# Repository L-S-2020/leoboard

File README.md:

# Leoboard

A makroboard I designed as a christmas present and my first project using 3d printing / cad design.
You can find the case design on onshape under: 
https://cad.onshape.com/documents/f016138659585157d187dc39/w/5da7c9f47346b58de636040e/e/736dc8079a6dc26abaf89305?renderMode=0&uiState=69bc84548cc73f69bd25787e

## Features
- 6 MX Style switches
- buzzer (for sound)
- rotary encoder
- rgb leds 
- rp2040 based

Note: The code folder also includes kmk and the necessary addons, so it can be directly flashed to the rp2040.

## Standard key binds
The board has 3 switchable layers:
|Layer| Rotary button | Rotary encoder | Button 1 | Button 2 | Button 3 | Button 4 | Button 5 | Button 6 |
|--|--|--|--|--|--|--|--|--|
| 1 (normal) | Mute | Volume | Play/ Pause | Next song | Previous song | Win+Shift+S | Task manager | Lock pc |
|2 (gaming) |Discord mute| Volume | Mute | Discord audio off | Medal save clip | Screenshot | M | I |
|3 (premiere pro) | \ | Seek through frames | Add cut | Delete clip | Zoom in | Zoom out | Undo | Redo |
|Setings| must be hold down | -- | Layer 1 | Layer 2 | Layer 3 | LED on/off | LED breathe animation |LED rainbow animation |

## The story
One day as I was editing a video for the video club at my school (check out the [yt channel](https://www.youtube.com/@gsgwaldkirch4155)), I was annoyed by the standard key assignments of Premiere Pro. Especially using the arrow keys to seek through frames manually (i.e. for finding the excact startframe of a clip) is a really slow process, so I thought, wouldn't it be cool to have a rotary knob for that and then also to have a special key set for directly placing cuts and zooming in the timeline? 

So I the idea to design my own macroboard was born. I found a nice starting tutorial on [the hackclub blueprint website](https://blueprint.hackclub.com/), which showed the ground ideas of macroboard design.
As it was just two weeks before christmas back then, I thought it would also be cool to use the board as a christmas present.

So I got started with the pcb design using kicad. The design itself is based on the seed xiao rp2040 devboard, as it is the perfect size and also quite cheap. Additionally to my initial requirements (switches and rotary encoder), I came up with the idea to also add leds for light and a buzzer for playing startup sounds.

Then I designed the pcb board and searched in the jlcpcb parts library for suiting (and cheap) parts. 

As the order was on its way, I started designing the case using onshape.

I also created an assembled model in onshape, to test the dimensions.

After printing and assembling the final macropads, I learned that, it's not good to make the inner dimensions of your case exactly like the dimensions of your board ;) , but fortunately, I printed everything in pla, so after some heating using a hair dryer, I could fit the pcb inside.

I then wrote a script for it, using kmk, as I liked the idea of being able to quickly change some configurations, without having to recompile. 
[@SillyGoose123](https://github.com/SillyGoose123) is also currently working on a more powerful, rust-based firmware for the board with a web based settings interface, check it out [here](https://github.com/SillyGoose123/MacroBoard).

##
A big thanks to my cs teacher for letting me print out the cases using the 3dprinter in his office and to [@SillyGoose123](https://github.com/SillyGoose123) for printing out the keycaps.

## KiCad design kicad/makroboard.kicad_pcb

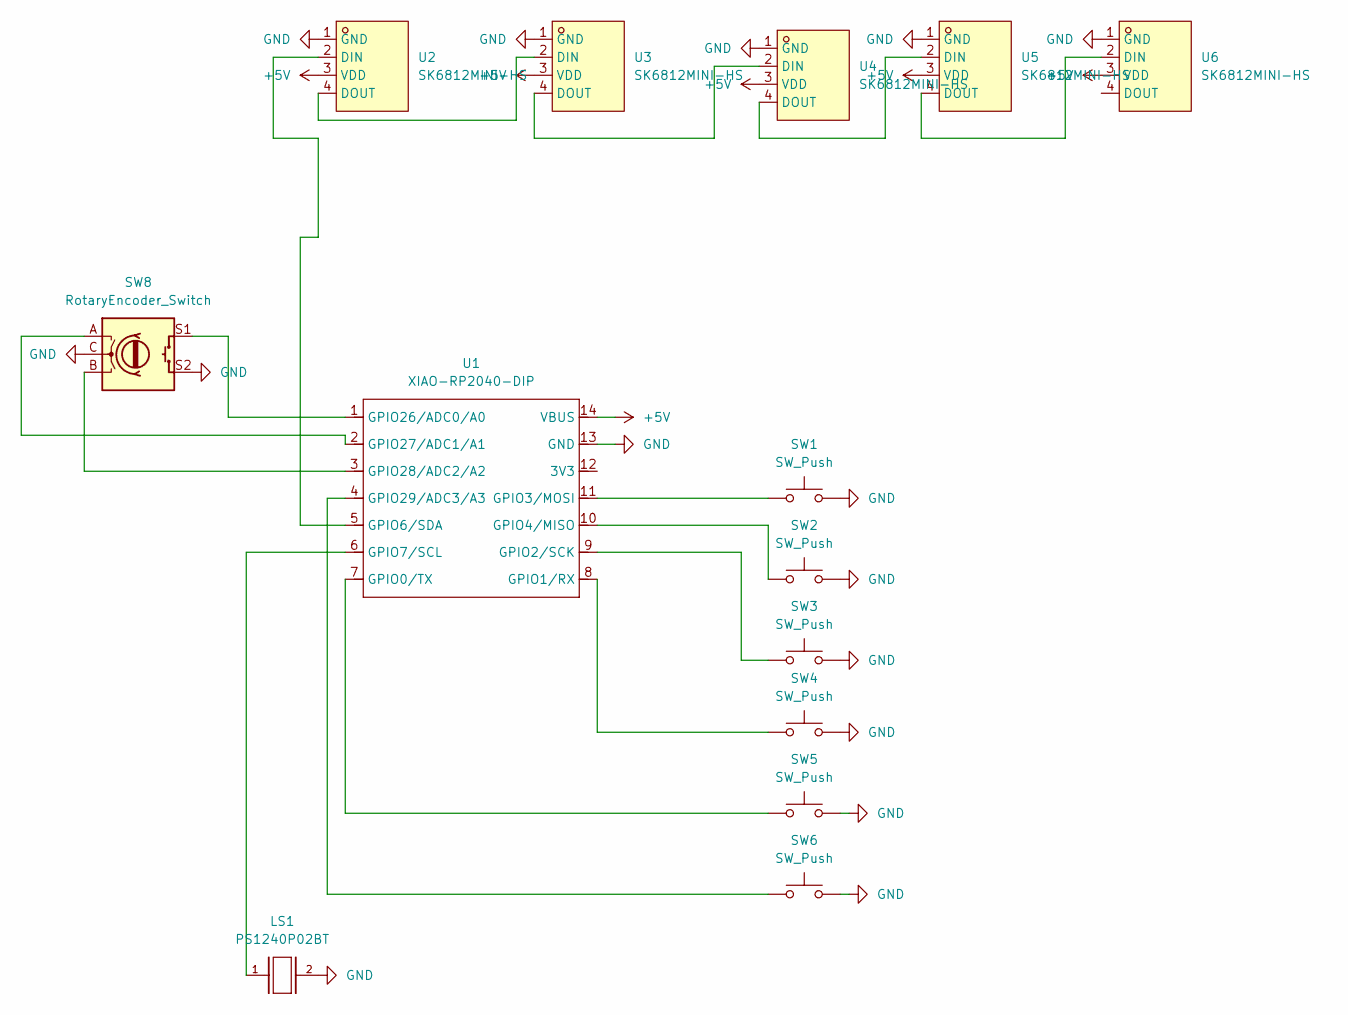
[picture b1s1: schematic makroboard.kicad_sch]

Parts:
LS1: PS1240P02BT; XDCR_PS1240P02BT
SW1, SW2, SW3, SW4, SW5, SW6: SW_Push; SW_Cherry_MX_1.00u_Plate
SW8: RotaryEncoder_Switch; RotaryEncoder_Alps_EC11E-Switch_Vertical_H20mm
U1: XIAO-RP2040-DIP
U2, U3, U4, U5, U6: SK6812MINI-HS; LED-SMD_4P-L3.5-W3.5-BR_SK6812MINI-HS; LCSC Part C2922787

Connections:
+5V: U1.14 (VBUS), U2.3 (VDD), U3.3 (VDD), U4.3 (VDD), U5.3 (VDD), U6.3 (VDD)
GND: LS1.2, SW1.2, SW2.2, SW3.2, SW4.2, SW5.2, SW6.2, SW8.C, SW8.S2, U1.13 (GND), U2.1 (GND), U3.1 (GND), U4.1 (GND), U5.1 (GND), U6.1 (GND)
unnamed: SW5.1, U1.7 (GPIO0/TX)
unnamed: SW4.1, U1.8 (GPIO1/RX)
unnamed: SW3.1, U1.9 (GPIO2/SCK)
unnamed: SW1.1, U1.11 (GPIO3/MOSI)
unnamed: SW2.1, U1.10 (GPIO4/MISO)
unnamed: U1.5 (GPIO6/SDA), U2.2 (DIN)
unnamed: LS1.1, U1.6 (GPIO7/SCL)
unnamed: SW8.S1, U1.1 (GPIO26/ADC0/A0)
unnamed: SW8.A, U1.2 (GPIO27/ADC1/A1)
unnamed: SW8.B, U1.3 (GPIO28/ADC2/A2)
unnamed: SW6.1, U1.4 (GPIO29/ADC3/A3)
unnamed: U2.4 (DOUT), U3.2 (DIN)
unnamed: U3.4 (DOUT), U4.2 (DIN)
unnamed: U4.4 (DOUT), U5.2 (DIN)
unnamed: U5.4 (DOUT), U6.2 (DIN)

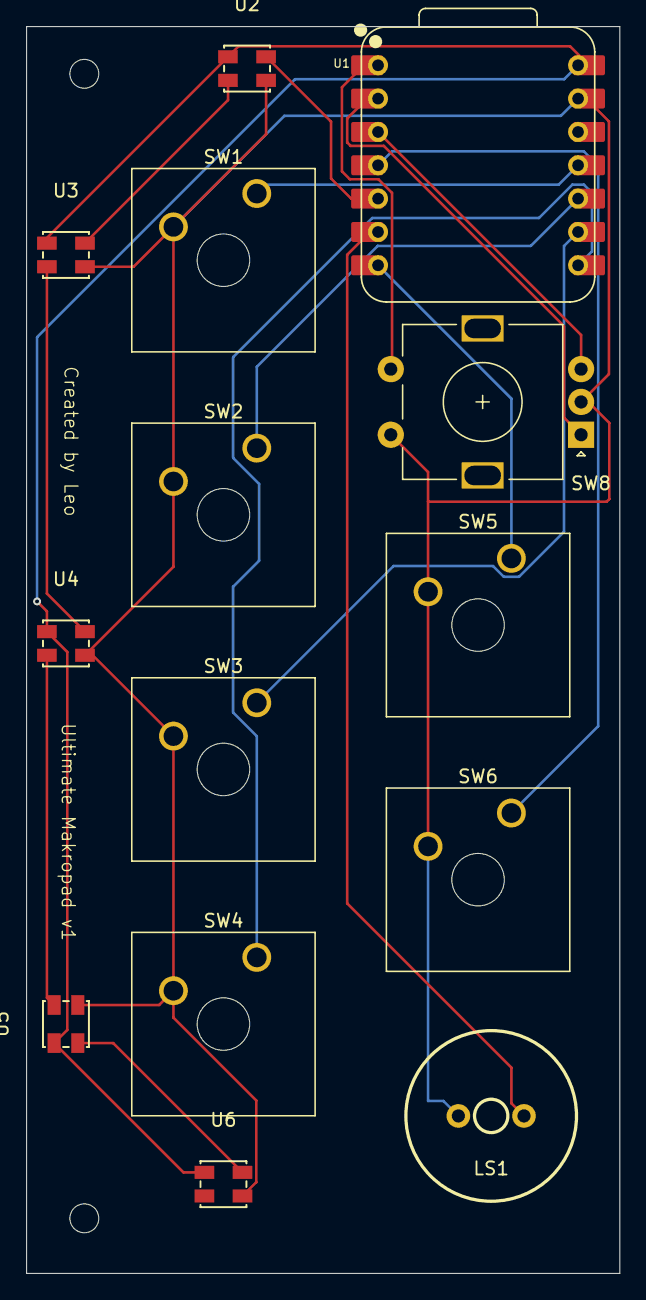
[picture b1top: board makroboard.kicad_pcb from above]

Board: 2 copper layers, 45.2 x 95.0 mm, 15 parts (0 on the bottom side), 17 nets.

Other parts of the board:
MT: MountingHole_2.2mm_M2_DIN965

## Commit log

2026-03-19 add files
2026-03-19 fix github formating issues
2026-03-19 add code
